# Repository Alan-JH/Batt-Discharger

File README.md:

# Batt-Discharger
High current battery storage discharger for TJ UAV

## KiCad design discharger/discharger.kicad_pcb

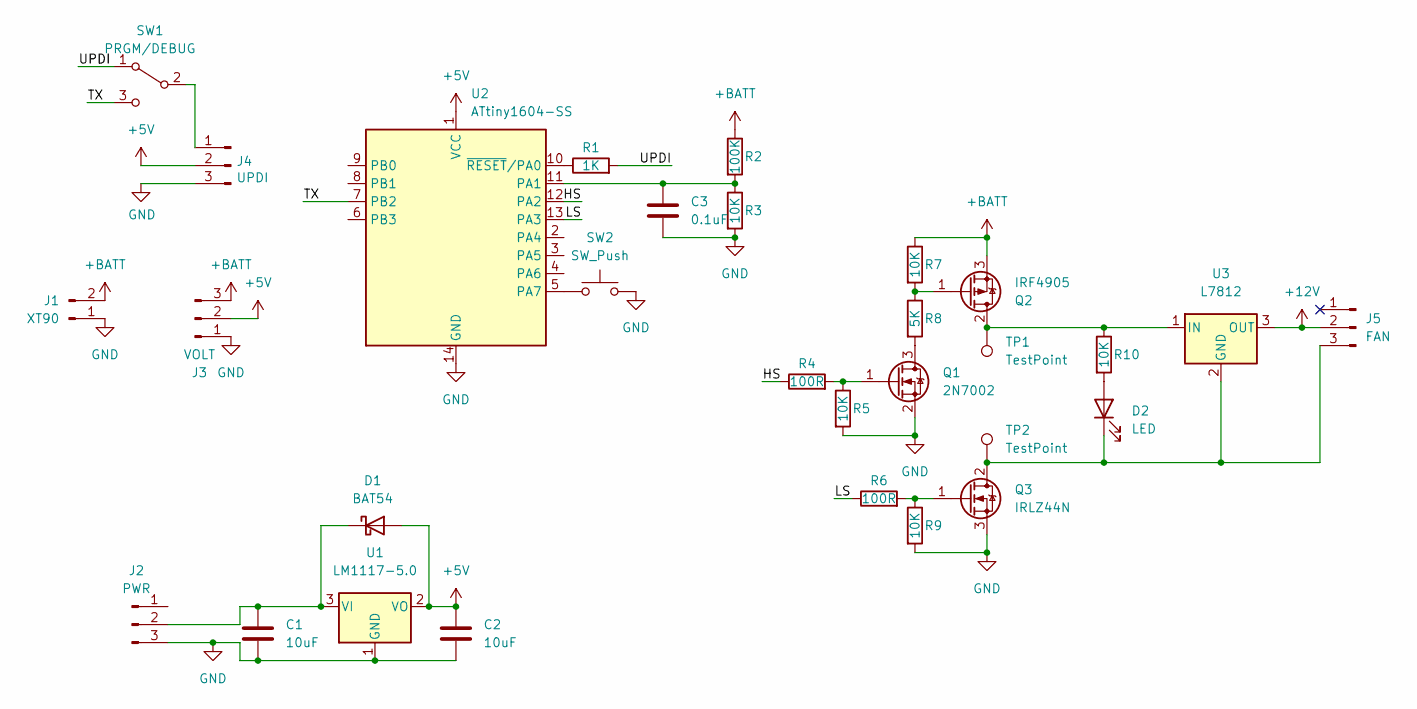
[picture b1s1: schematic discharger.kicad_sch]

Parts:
C1, C2: 10uF; C_0805_2012Metric
C3: 0.1uF; C_0805_2012Metric
D1: BAT54; D_SOD-123
D2: LED; LED_D5.0mm
J1: XT90
J2: PWR; PinHeader_1x03_P2.54mm_Vertical
J3: VOLT; BattMonitor
J4: UPDI; PinHeader_1x03_P2.54mm_Vertical
J5: FAN; PinHeader_1x03_P2.54mm_Vertical
Q1: 2N7002; SOT-23
Q2: IRF4905; TO-220-3_Horizontal_TabDown
Q3: IRLZ44N; TO-220-3_Horizontal_TabDown
R1: 1K; R_1206_3216Metric
R2: 100K; R_1206_3216Metric
R3, R5, R7, R9, R10: 10K; R_1206_3216Metric
R4, R6: 100R; R_1206_3216Metric
R8: 5K; R_1206_3216Metric
SW1: PRGM/DEBUG; SW_Slide_1P2T_CK_OS102011MS2Q
SW2: SW_Push; SW_PUSH_6mm
TP1, TP2: TestPoint; MountingHole_3.2mm_M3_DIN965_Pad
U1: LM1117-5.0; SOT-223-3_TabPin2
U2: ATtiny1604-SS; SOIC-14_3.9x8.7mm_P1.27mm
U3: L7812; TO-220-3_Horizontal_TabDown

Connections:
+12V: J5.2, U3.3 (OUT)
+BATT: J1.2, J3.3, Q2.3 (S), R2.1, R7.1
/HS: R4.1, U2.12 (PA2)
/LS: R6.1, U2.13 (PA3)
/TX: SW1.3 (C), U2.7 (PB2)
/UPDI: R1.2, SW1.1 (A)
GND: C1.2, C2.2, C3.2, J1.1, J2.3, J3.1, J4.3, Q1.2 (S), Q3.3 (S), R3.2, R5.2, R9.2, SW2.2, U1.1 (GND), U2.14 (GND)
unnamed: C1.1, D1.1 (K), J2.2, U1.3 (VI)
unnamed: C3.1, R2.2, R3.1, U2.11 (PA1)
unnamed: D2.1 (K), J5.3, Q3.2 (D), TP2.1, U3.2 (GND)
unnamed: D2.2 (A), R10.2
unnamed: J4.1, SW1.2 (B)
unnamed: Q1.1 (G), R4.2, R5.1
unnamed: Q1.3 (D), R8.2
unnamed: Q2.1 (G), R7.2, R8.1
unnamed: Q2.2 (D), R10.1, TP1.1, U3.1 (IN)
unnamed: Q3.1 (G), R6.2, R9.1
unnamed: R1.1, U2.10 (~RESET/PA0)
unnamed: SW2.1, U2.5 (PA7)

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
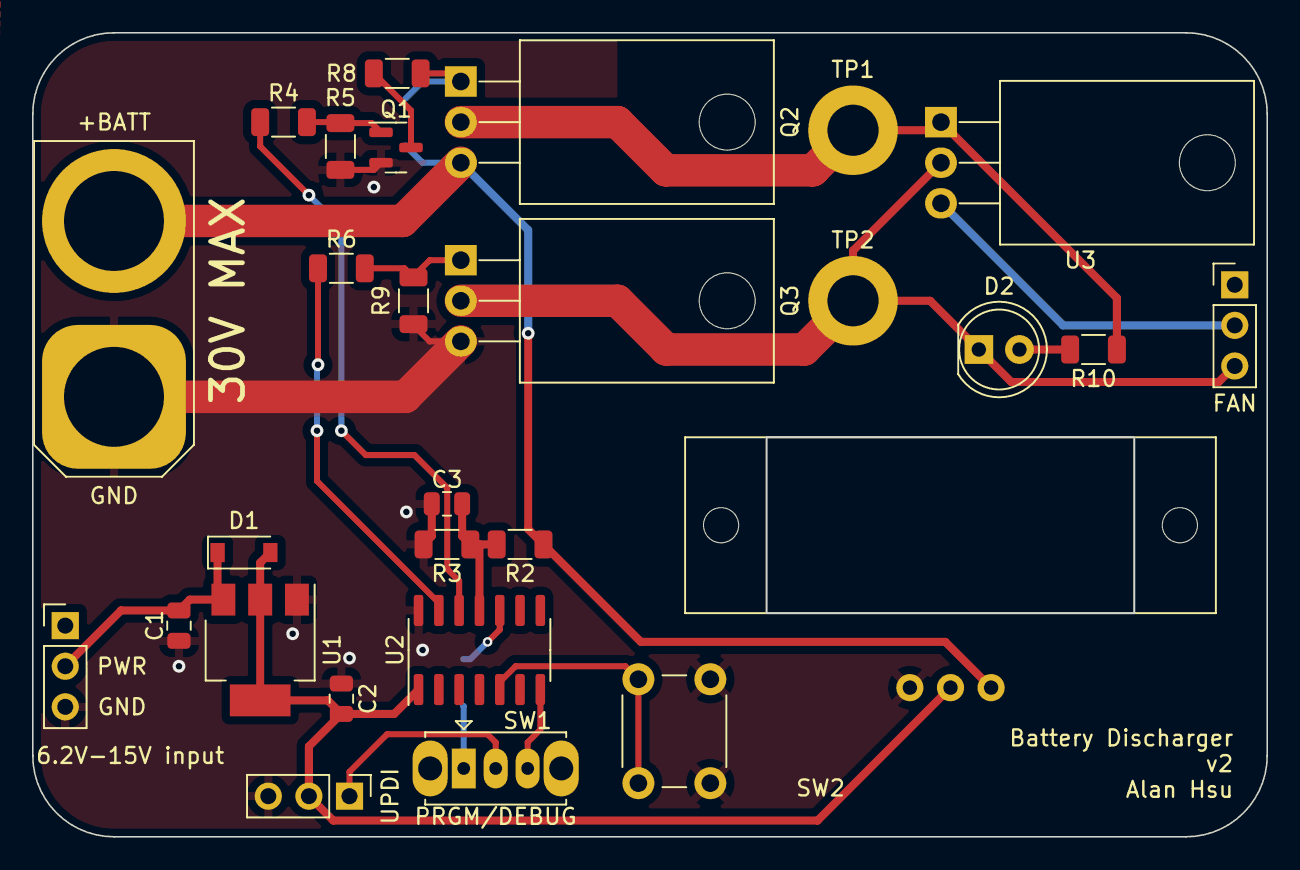
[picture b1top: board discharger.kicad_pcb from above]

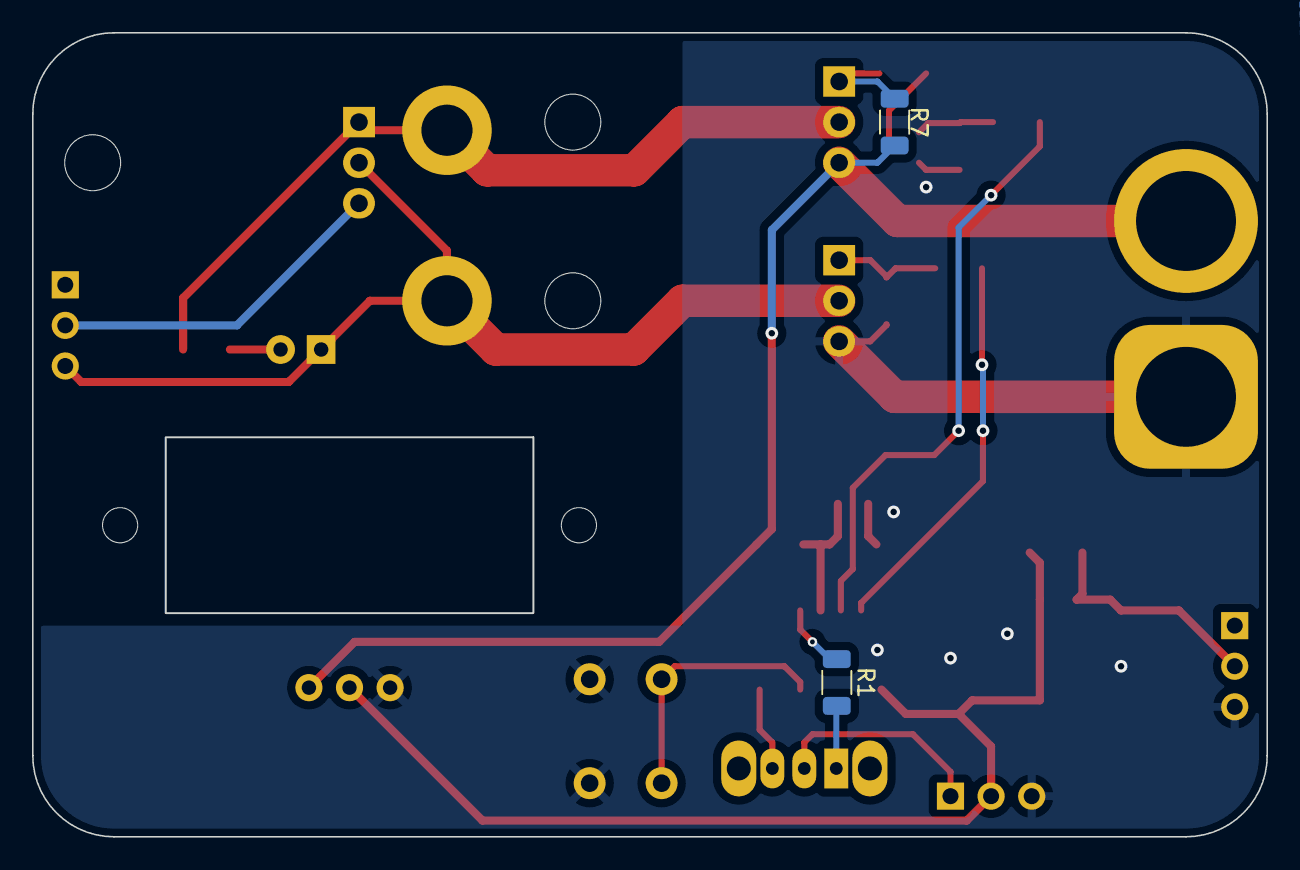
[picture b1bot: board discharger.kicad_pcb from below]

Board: 2 copper layers, 77.2 x 50.3 mm, 30 parts (2 on the bottom side), 20 nets.

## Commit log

2022-09-12 initial schematic and footprints
2022-10-27 finish routing and gerbers
2022-10-27 gitignore fix
2022-10-31 correct max input voltage, STEP export
2022-10-31 fix xt90 pth size
2022-11-10 code
2022-11-11 finish code
2022-11-11 5V instead of 3.3V
2022-11-14 read Vcc
2022-11-16 finish software
